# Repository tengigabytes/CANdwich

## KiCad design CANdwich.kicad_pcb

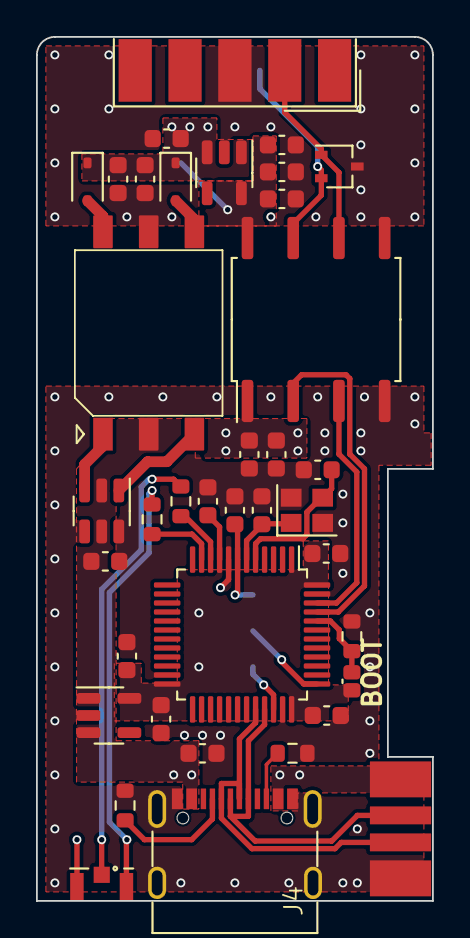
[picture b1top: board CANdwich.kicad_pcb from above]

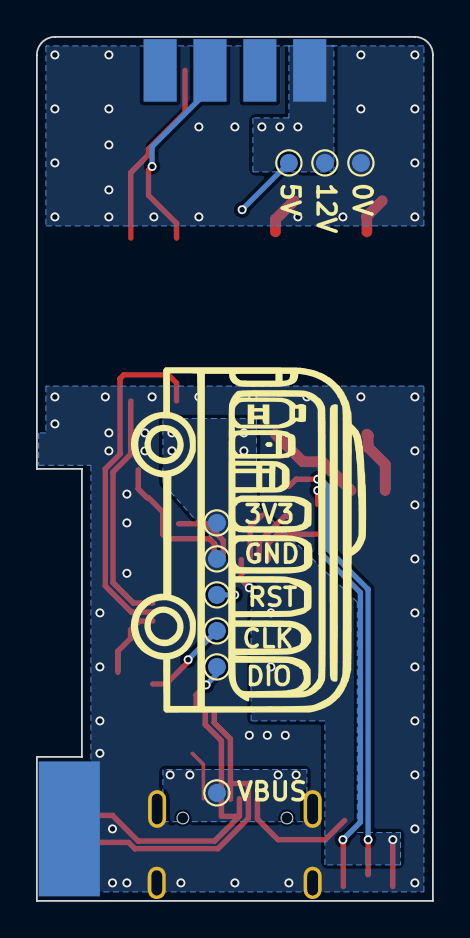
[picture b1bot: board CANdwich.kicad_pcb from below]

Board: 2 copper layers, 22.0 x 48.0 mm, 47 parts (9 on the bottom side), 28 nets.

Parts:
C1, C2: 8p; C_0603_1608Metric
C3, C4, C5, C6, C7, C20, C24, C25: 100n; C_0603_1608Metric
C8, C9, C22, C23, C26, C27: 1u; C_0603_1608Metric
C18, C19: 10u; C_0603_1608Metric
D1: LTST-S326KGJRKT_RG; LED_LiteOn_LTST-S326
D3, D4: NSR1020MW2T1G; D_SOD-323
D5: PESD1CAN-U; SOT-323_SC-70
J1: DE9_Receptacle; DSUB-9_Male_EdgeMount_P2.77mm
J2: USB_C_Receptacle_USB2.0; USB_C_Receptacle_XKB_U262-16XN-4BVC11
J4: Conn_01x04_Socket; USB_EdgeMount
R1: 10k; R_0603_1608Metric
R2, R3: 5.1k; R_0603_1608Metric
R4, R5, R7: 150; R_0603_1608Metric
TP1, TP2, TP3, TP4, TP5, TP6, TP7, TP8, TP9: TestPoint; TestPoint_Pad_D1.0mm
TR1: Wuerth_750316819; Transformer_Wuerth_750315371
U1: AP2127K-3.3; SOT-23-5
U2: STM32F072CBT6; LQFP-48_7x7mm_P0.5mm
U3: SN6505BDBV; SOT-23-6
U4: AP2204K-5.0TRG1; SOT-23-5
U6: ISO1050DUB; SOP-8_6.62x9.15mm_P2.54mm
Y1: 16MHz; Crystal_SMD_2520-4Pin_2.5x2.0mm

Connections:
+5VD: C23.2, C24.1, C26.2, TP4.1, U4.5 (VOUT), U6.8 (VCC2)
+12V: C19.1, C20.1, C22.2, D3.1 (K), D4.1 (K), J1.9, TP3.1, U4.1 (VIN), U4.3 (EN)
/BOOT0: R1.2, R7.1, U2.44 (BOOT0)
/CANH: D5.2 (C2), J1.7, U6.7 (CANH)
/CANL: D5.1 (C1), J1.2, U6.6 (CANL)
/CAN_RX: U2.45 (PB8), U6.2 (RXD)
/CAN_TX: U2.46 (PB9), U6.3 (TXD)
/LED_RX: R5.1, U2.11 (PA1)
/LED_TX: R4.1, U2.10 (PA0)
/SWCLK: TP6.1, U2.37 (PA14)
/SWDIO: TP5.1, U2.34 (PA13)
/USB_D+: J2.A6 (D+), J2.B6 (D+), J4.3, U2.33 (PA12)
/USB_D-: J2.A7 (D-), J2.B7 (D-), J4.2, U2.32 (PA11)
/clk_N: C2.2, U2.6 (PF1), Y1.1
/clk_P: C1.2, U2.5 (PF0), Y1.3
/nRST: C3.1, TP7.1, U2.7 (NRST)
Earth: C1.1, C2.1, C3.2, C4.1, C5.1, C6.1, C7.1, C8.1, C9.1, C18.2, C25.2, C27.1, J2.A1 (GND), J2.A12 (GND), J2.B1 (GND), J2.B12 (GND), J2.S1 (SHIELD), J4.4, R1.1, R2.2, R3.2, TP9.1, U1.2 (GND), U2.8 (VSSA), U2.23 (VSS), U2.35 (VSS), U2.47 (VSS), U3.4 (GND), U3.6 (CLK), U6.4 (GND1), Y1.2, Y1.4
GNDA: C19.2, C20.2, C22.1, C23.1, C24.2, C26.1, D5.3 (CC), J1.3, TP8.1, TR1.5, U4.2 (GND), U6.5 (GND2)
unnamed: D1.1 (K1), R5.2
unnamed: D1.2 (K2), R4.2
unnamed: D3.2 (A), TR1.4
unnamed: D4.2 (A), TR1.6
unnamed: J2.A5 (CC1), R2.1
unnamed: J2.B5 (CC2), R3.1
unnamed: TR1.3, U3.1 (D1)
unnamed: TR1.1, U3.3 (D2)
VBUS: C8.2, C18.1, J2.A4 (VBUS), J2.A9 (VBUS), J2.B4 (VBUS), J2.B9 (VBUS), J4.1, TP1.1, TR1.2, U1.1 (VIN), U1.3 (EN), U3.2 (VCC), U3.5 (EN)
VD3V3: C4.2, C5.2, C6.2, C7.2, C9.2, C25.1, C27.2, D1.3 (A), R7.2, TP2.1, U1.5 (VOUT), U2.1 (VBAT), U2.9 (VDDA), U2.24 (VDD), U2.36 (VDDIO2), U2.48 (VDD), U6.1 (VCC1)

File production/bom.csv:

Designator,Footprint,Quantity,Value,LCSC Part #
"C1, C2",0603,2,8p,C726543
"C18, C19",0603,2,10u,C109457
"C20, C24, C25, C3, C4, C5, C6, C7",0603,8,100n,C149620
"C22, C23, C26, C27, C8, C9",0603,6,1u,C726560
D2,LED_LiteOn_LTST-C19HE1WT,1,LED_RGBA,C458749
"D3, D4",D_SOD-323,2,NSR1020MW2T1G,C116953
D5,SOT-323_SC-70,1,PESD1CAN-U,C152727
J2,USB_C_Receptacle_XKB_U262-16XN-4BVC11,1,USB_C_Receptacle_USB2.0,C319148
J4,USB_snowflake,1,Conn_01x04_Socket,
R1,0603,1,10k,C98220
"R2, R3",0603,2,5.1k,C105580
"R4, R5, R6, R7",0603,4,150,C114608
TR1,Transformer_Wuerth_750315371,1,Wuerth_750316819,C5184245
U1,SOT-23-5,1,AP2127K-3.3,C156285
U2,LQFP-48_7x7mm_P0.5mm,1,STM32F072CBT6,C81720
U3,SOT-23-6,1,SN6505BDBV,C74518
U4,SOT-23-5,1,AP2204K-5.0TRG1,C112031
U6,SOP-8_6.62x9.15mm_P2.54mm,1,ISO1050DUB,C16428
Y1,Crystal_SMD_2520-4Pin_2.5x2.0mm,1,16MHz,C280836

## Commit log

2023-06-11 7.02 base line
2023-06-11 Placement in KICAD V7.0.5
2023-06-13 Snapshot for layout
2023-06-17 resize edge.cuts
2023-06-18 V1.0 Generate external enclosure
2023-06-22 Change USB edge connection interface
2023-06-24 Change indication LED
